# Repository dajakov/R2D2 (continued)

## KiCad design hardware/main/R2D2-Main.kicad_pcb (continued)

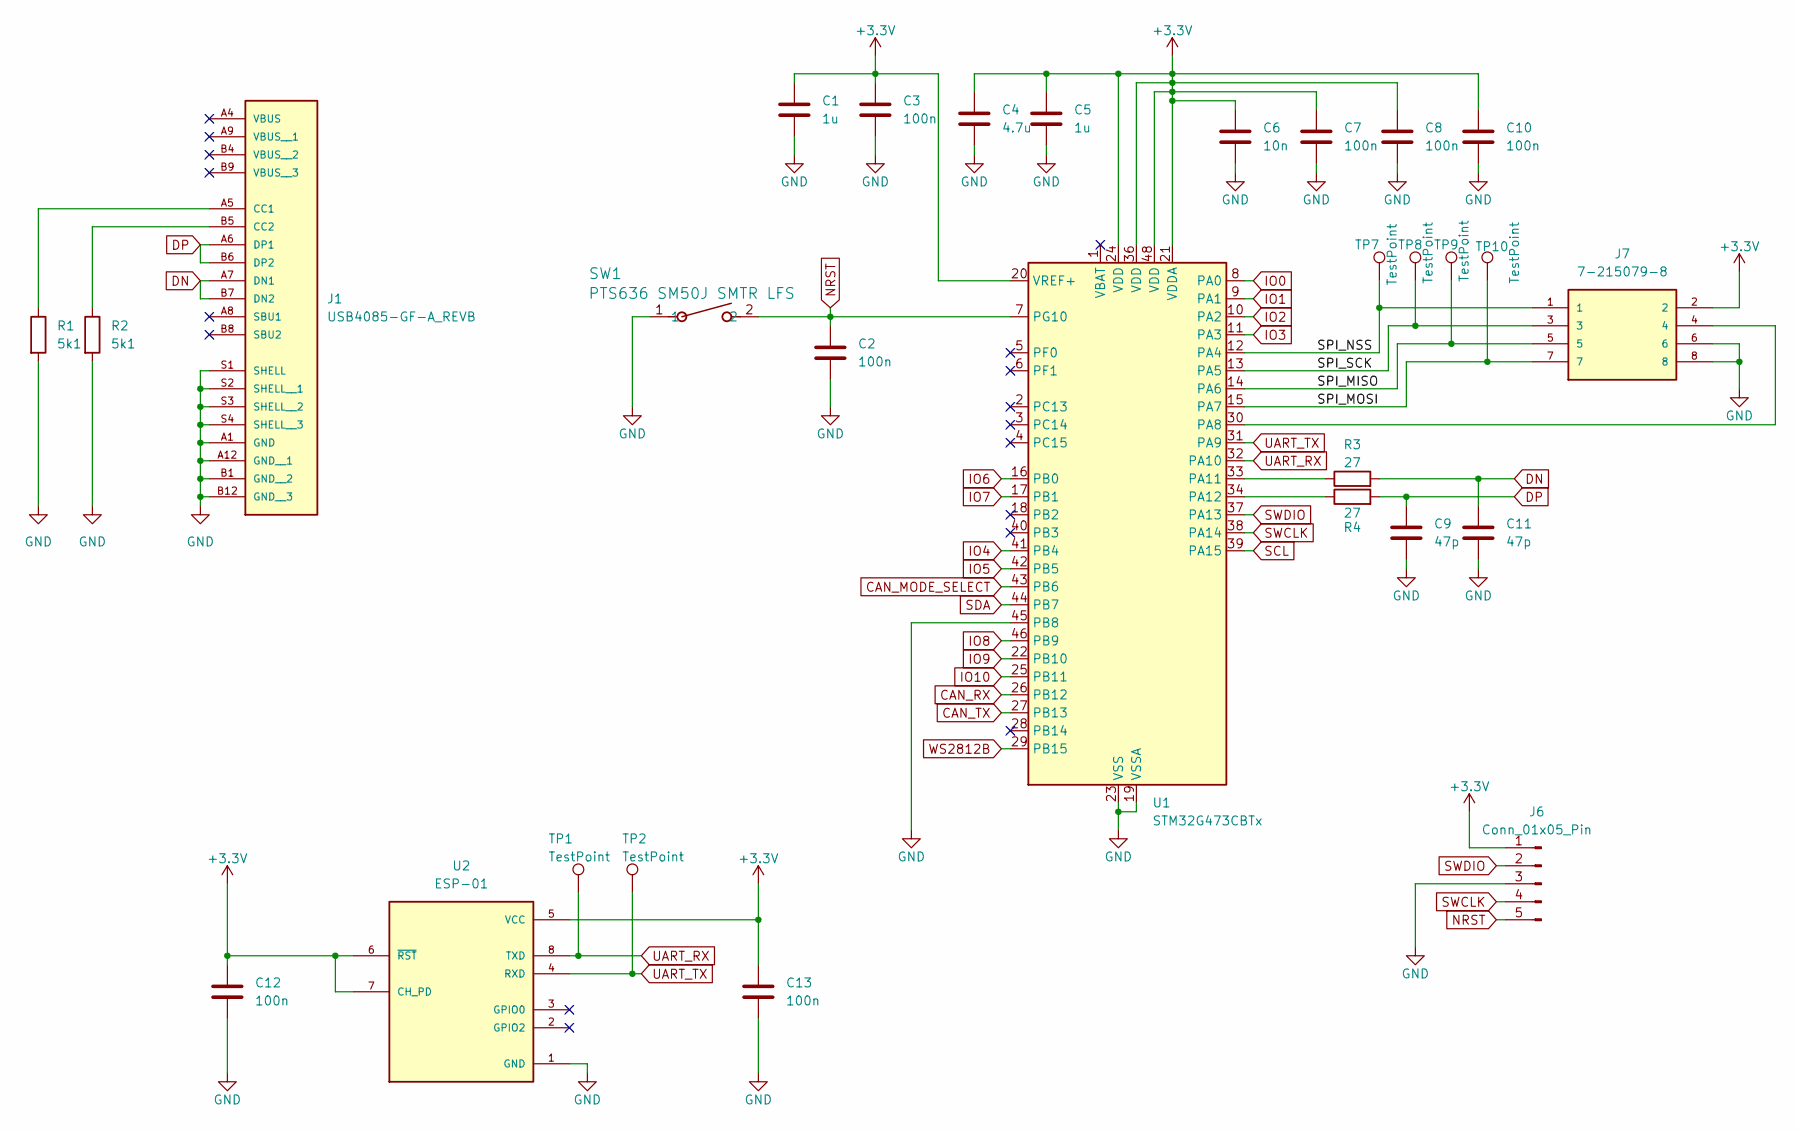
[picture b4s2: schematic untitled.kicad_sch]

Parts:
C1, C5: 1u; C_0603_1608Metric_Pad1.08x0.95mm_HandSolder
C2, C3, C7, C8, C10, C12, C13: 100n; C_0603_1608Metric_Pad1.08x0.95mm_HandSolder
C4: 4.7u; C_0603_1608Metric_Pad1.08x0.95mm_HandSolder
C6: 10n; C_0603_1608Metric_Pad1.08x0.95mm_HandSolder
C9, C11: 47p; C_0603_1608Metric_Pad1.08x0.95mm_HandSolder
J1: USB4085-GF-A_REVB; GCT_USB4085-GF-A_REVB; PARTREV B
J6: Conn_01x05_Pin; PinHeader_1x05_P2.54mm_Vertical
J7: 7-215079-8; TE_7-215079-8; PARTREV Y1
R1, R2: 5k1; R_0603_1608Metric_Pad0.98x0.95mm_HandSolder
R3, R4: 27; R_0603_1608Metric_Pad0.98x0.95mm_HandSolder
SW1: PTS636 SM50J SMTR LFS; SW_PTS636_CNK
TP1, TP2, TP7, TP8, TP9, TP10: TestPoint; TestPoint_Pad_D1.0mm
U1: STM32G473CBTx; LQFP48-7x7mm
U2: ESP-01; MODULE_ESP-01; PARTREV 1.0

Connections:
+3.3V: C1.1, C3.1, C4.1, C5.1, C6.1, C7.1, C8.1, C10.1, C12.1, C13.1, J6.1, J7.2, U1.20 (VREF+), U1.21 (VDDA), U1.24 (VDD), U1.36 (VDD), U1.48 (VDD), U2.5 (VCC), U2.6 (~RST), U2.7 (CH_PD); also elsewhere on the board
/Untitled Sheet/SPI_MISO: J7.5, TP9.1, U1.14 (PA6)
/Untitled Sheet/SPI_MOSI: J7.7, TP10.1, U1.15 (PA7)
/Untitled Sheet/SPI_NSS: J7.1, TP7.1, U1.12 (PA4)
/Untitled Sheet/SPI_SCK: J7.3, TP8.1, U1.13 (PA5)
CAN_MODE_SELECT: U1.43 (PB6); also elsewhere on the board
CAN_RX: U1.26 (PB12); also elsewhere on the board
CAN_TX: U1.27 (PB13); also elsewhere on the board
DN: C11.1, J1.A7 (DN1), J1.B7 (DN2), R3.2
DP: C9.1, J1.A6 (DP1), J1.B6 (DP2), R4.2
GND: C1.2, C2.2, C3.2, C4.2, C5.2, C6.2, C7.2, C8.2, C9.2, C10.2, C11.2, C12.2, C13.2, J1.A1 (GND), J1.A12 (GND__1), J1.B1 (GND__2), J1.B12 (GND__3), J1.S1 (SHELL), J1.S2 (SHELL__1), J1.S3 (SHELL__2), J1.S4 (SHELL__3), J6.3, J7.6, J7.8, R1.2, R2.2, SW1.1, U1.19 (VSSA), U1.23 (VSS), U1.35 (VSS), U1.45 (PB8), U1.47 (VSS), U2.1 (GND); also elsewhere on the board
IO0: U1.8 (PA0); also elsewhere on the board
IO1: U1.9 (PA1); also elsewhere on the board
IO2: U1.10 (PA2); also elsewhere on the board
IO3: U1.11 (PA3); also elsewhere on the board
IO4: U1.41 (PB4); also elsewhere on the board
IO5: U1.42 (PB5); also elsewhere on the board
IO6: U1.16 (PB0); also elsewhere on the board
IO7: U1.17 (PB1); also elsewhere on the board
IO8: U1.46 (PB9); also elsewhere on the board
IO9: U1.22 (PB10); also elsewhere on the board
IO10: U1.25 (PB11); also elsewhere on the board
NRST: C2.1, J6.5, SW1.2, U1.7 (PG10)
unnamed: J1.A5 (CC1), R1.1
unnamed: J1.B5 (CC2), R2.1
unnamed: J7.4, U1.30 (PA8)
unnamed: R3.1, U1.33 (PA11)
unnamed: R4.1, U1.34 (PA12)
SCL: U1.39 (PA15); also elsewhere on the board
SDA: U1.44 (PB7); also elsewhere on the board
SWCLK: J6.4, U1.38 (PA14)
SWDIO: J6.2, U1.37 (PA13)
UART_RX: TP1.1, U1.32 (PA10), U2.8 (TXD)
UART_TX: TP2.1, U1.31 (PA9), U2.4 (RXD)
WS2812B: U1.29 (PB15); also elsewhere on the board

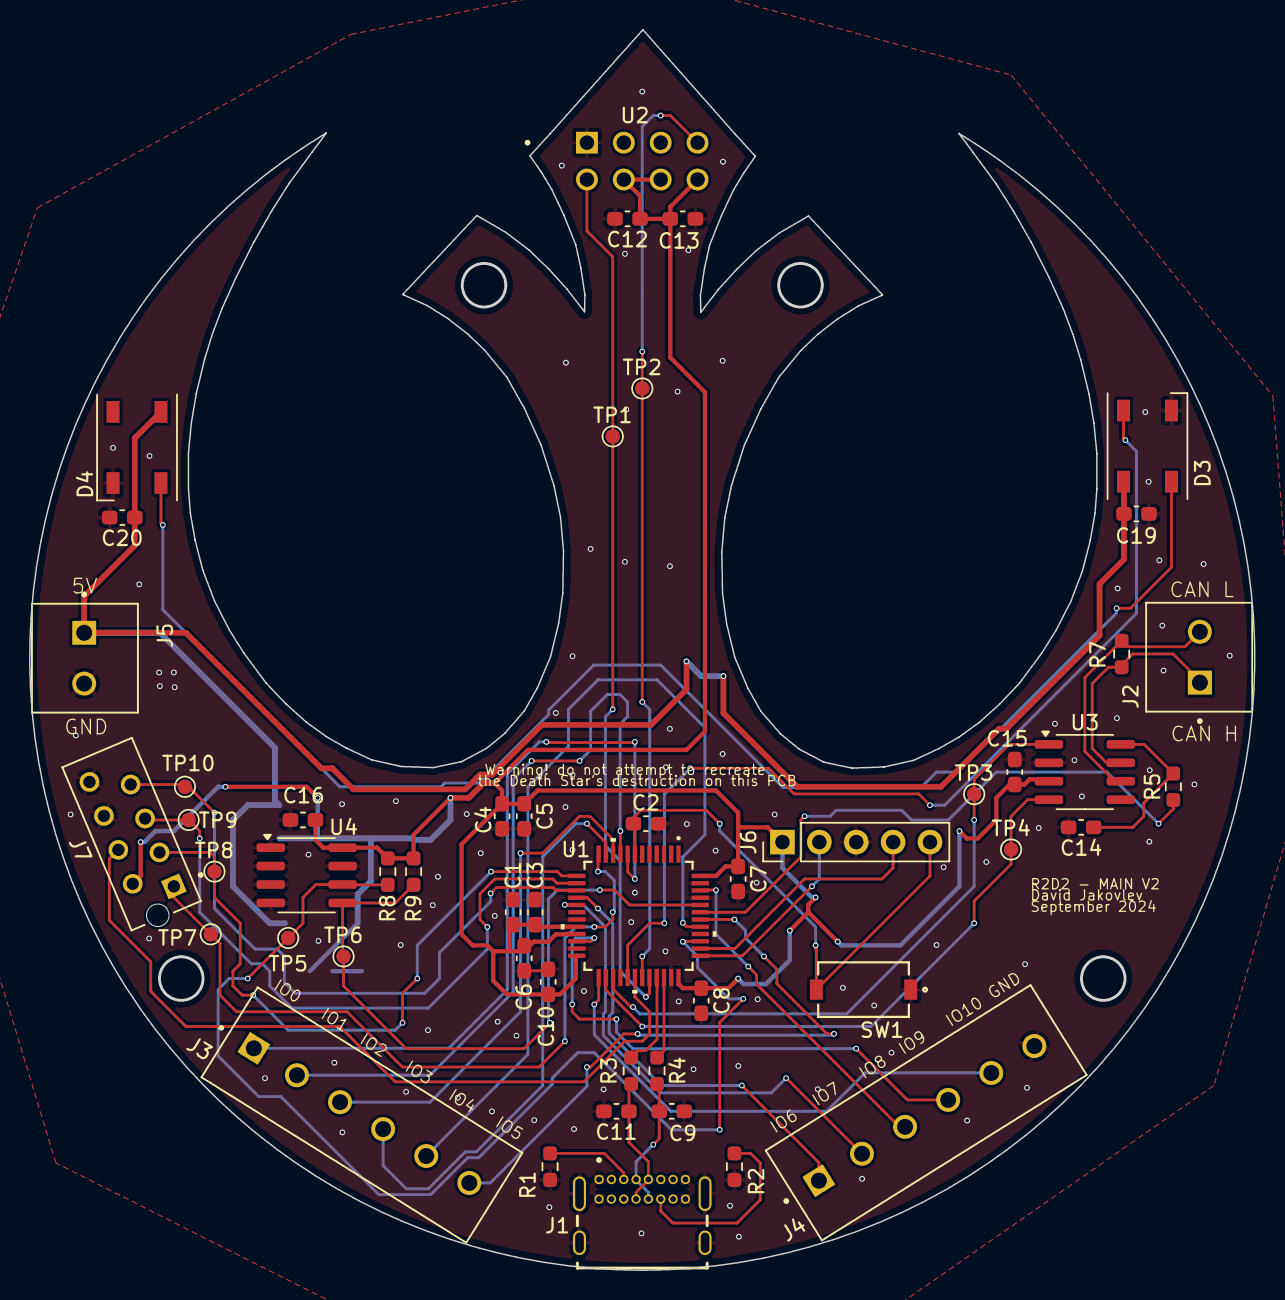
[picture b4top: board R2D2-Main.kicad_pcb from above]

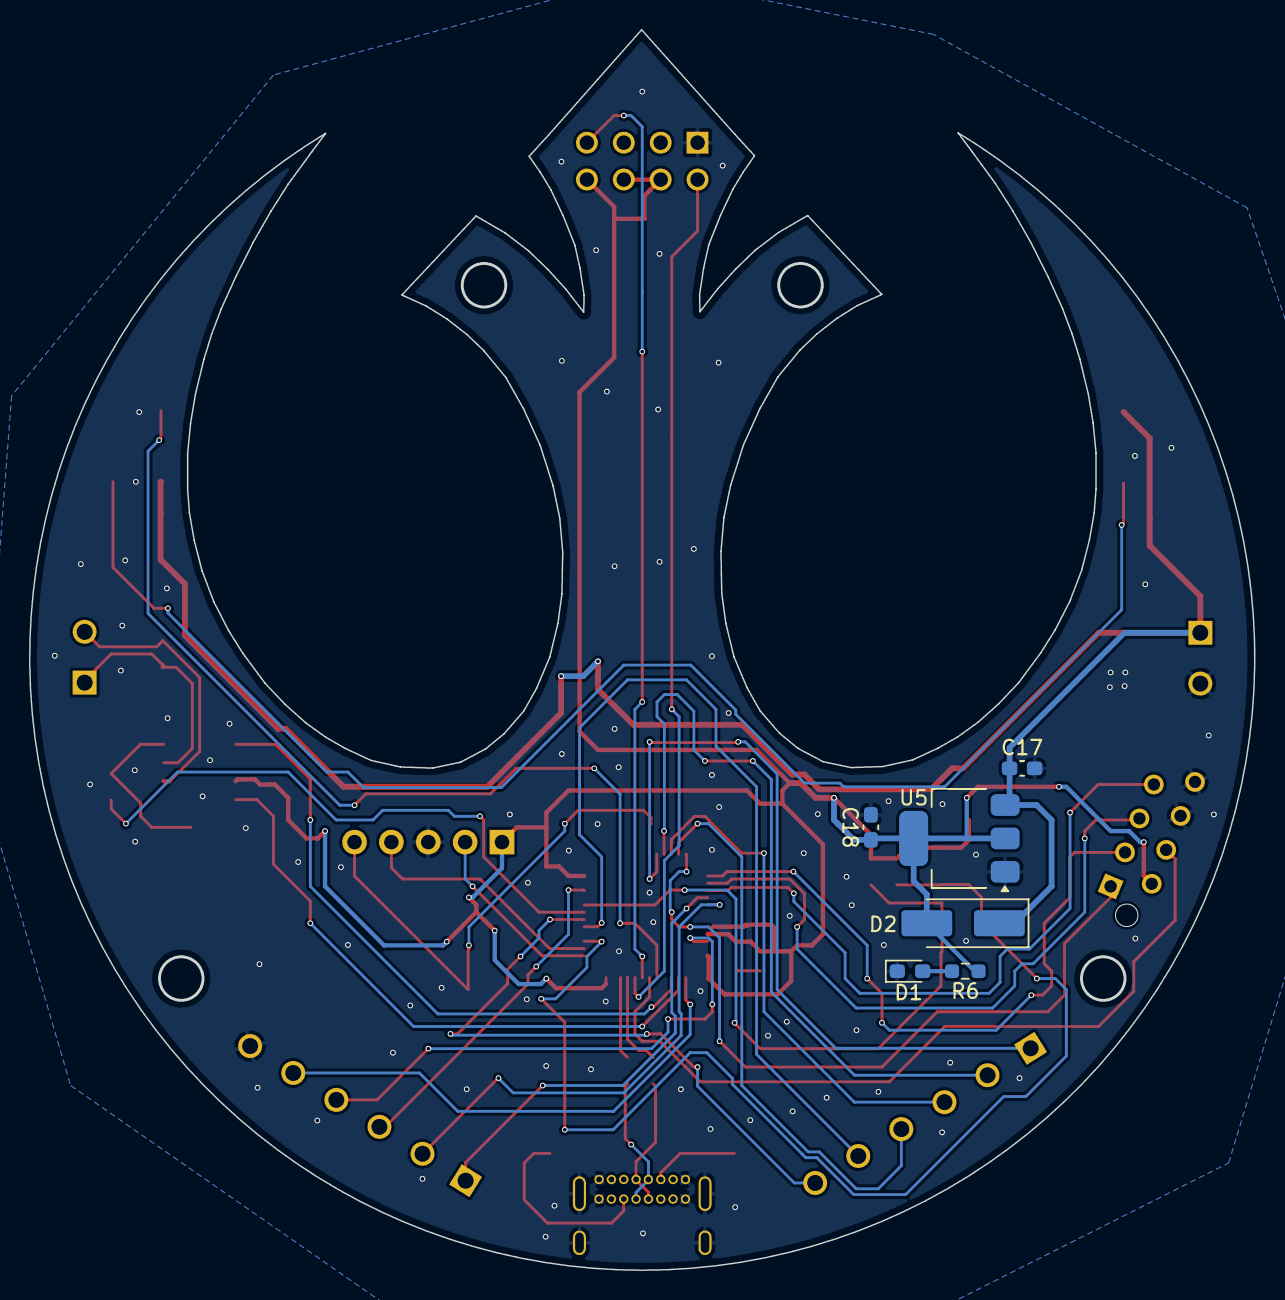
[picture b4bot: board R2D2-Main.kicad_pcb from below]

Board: 2 copper layers, 84.3 x 85.3 mm, 56 parts (6 on the bottom side), 41 nets.

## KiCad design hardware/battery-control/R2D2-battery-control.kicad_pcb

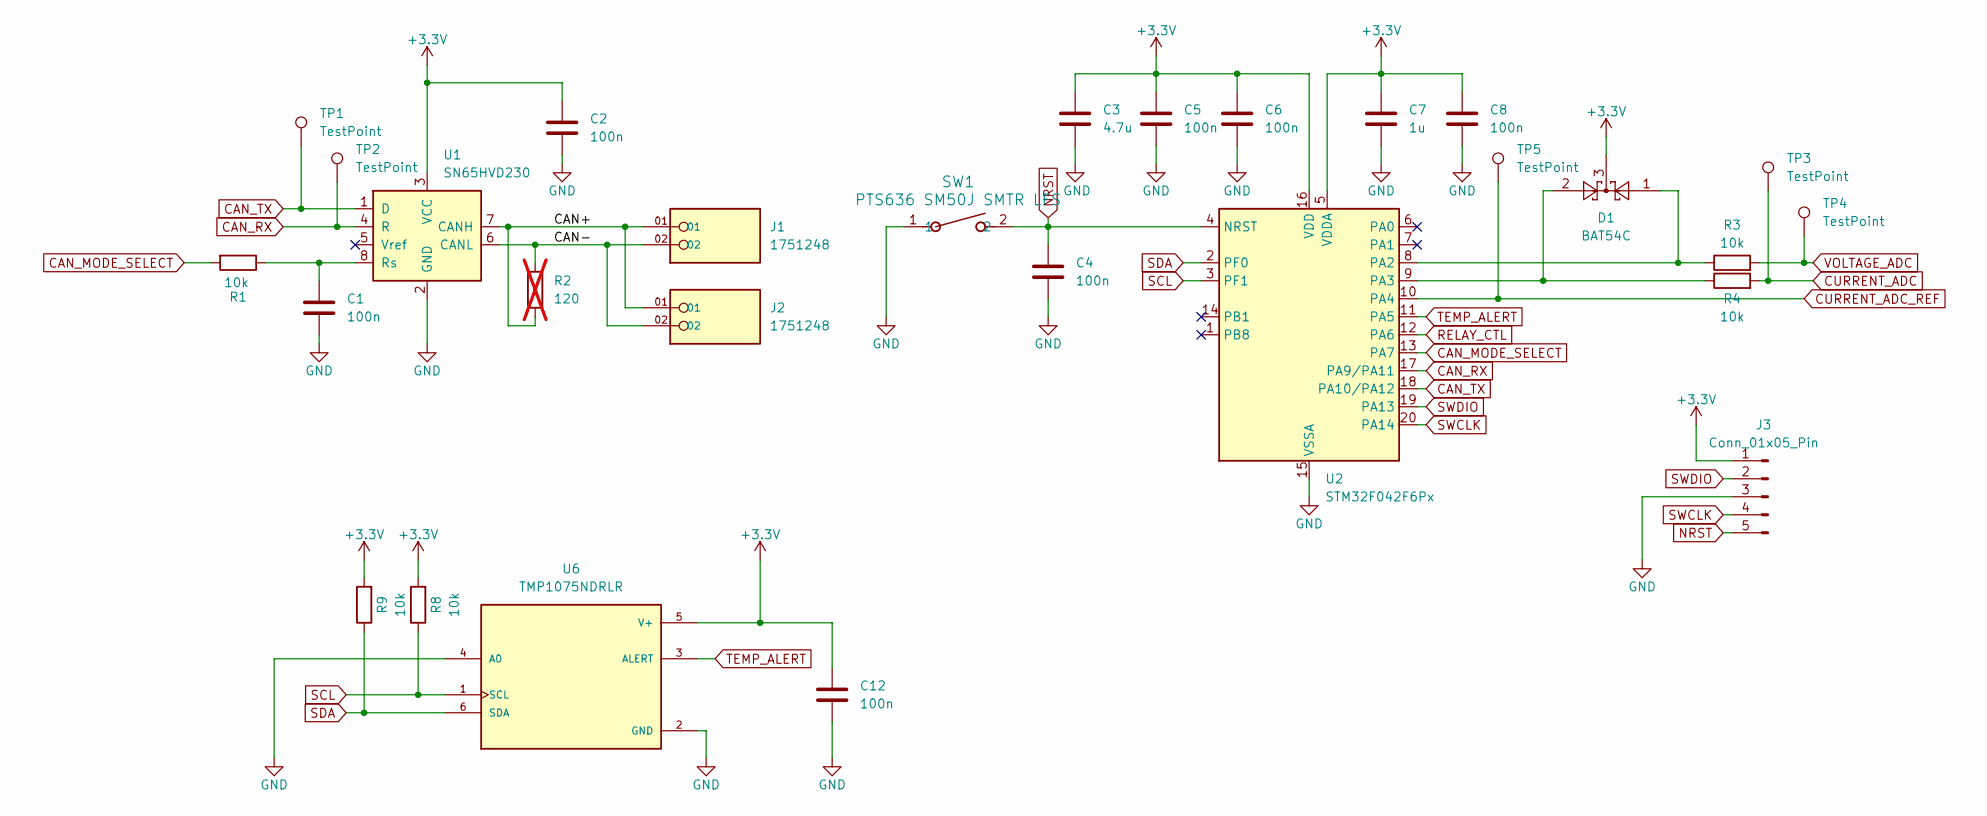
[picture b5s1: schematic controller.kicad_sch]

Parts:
C1, C2, C4, C5, C6, C8, C12: 100n; C_0603_1608Metric_Pad1.08x0.95mm_HandSolder
C3: 4.7u; C_0603_1608Metric_Pad1.08x0.95mm_HandSolder
C7: 1u; C_0603_1608Metric_Pad1.08x0.95mm_HandSolder
D1: BAT54C; SOT-23
J1, J2: 1751248; PHOENIX_1751248; PARTREV 03.03.2021
J3: Conn_01x05_Pin; PinHeader_1x05_P2.54mm_Horizontal
R1, R3, R4, R8, R9: 10k; R_0603_1608Metric_Pad0.98x0.95mm_HandSolder
R2: 120; R_0603_1608Metric_Pad0.98x0.95mm_HandSolder; not fitted
SW1: PTS636 SM50J SMTR LFS; SW_PTS636_CNK
TP1, TP2, TP3, TP4, TP5: TestPoint; TestPoint_Pad_D1.0mm
U1: SN65HVD230; SOIC-8_3.9x4.9mm_P1.27mm
U2: STM32F042F6Px; TSSOP-20_4.4x6.5mm_P0.65mm
U6: TMP1075NDRLR; SOT50P160X60-6N; PARTREV E

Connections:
+3.3V: C2.1, C3.1, C5.1, C6.1, C7.1, C8.1, C12.1, D1.3, J3.1, R8.2, R9.2, U1.3 (VCC), U2.5 (VDDA), U2.16 (VDD), U6.5 (V+); also elsewhere on the board
/controller/CAN+: J1.01, J2.01, R2.2, U1.7 (CANH)
/controller/CAN-: J1.02, J2.02, R2.1, U1.6 (CANL)
CAN_MODE_SELECT: R1.2, U2.13 (PA7)
CAN_RX: TP2.1, U1.4 (R), U2.17 (PA9/PA11)
CAN_TX: TP1.1, U1.1 (D), U2.18 (PA10/PA12)
CURRENT_ADC: R4.2, TP3.1; also elsewhere on the board
CURRENT_ADC_REF: TP5.1, U2.10 (PA4); also elsewhere on the board
GND: C1.2, C2.2, C3.2, C4.2, C5.2, C6.2, C7.2, C8.2, C12.2, J3.3, SW1.1, U1.2 (GND), U2.15 (VSSA), U6.2 (GND), U6.4 (A0); also elsewhere on the board
NRST: C4.1, J3.5, SW1.2, U2.4 (NRST)
unnamed: C1.1, R1.1, U1.8 (Rs)
unnamed: D1.1, R3.1, U2.8 (PA2)
unnamed: D1.2, R4.1, U2.9 (PA3)
RELAY_CTL: U2.12 (PA6); also elsewhere on the board
SCL: R8.1, U2.3 (PF1), U6.1 (SCL)
SDA: R9.1, U2.2 (PF0), U6.6 (SDA)
SWCLK: J3.4, U2.20 (PA14)
SWDIO: J3.2, U2.19 (PA13)
TEMP_ALERT: U2.11 (PA5), U6.3 (ALERT)
VOLTAGE_ADC: R3.2, TP4.1; also elsewhere on the board

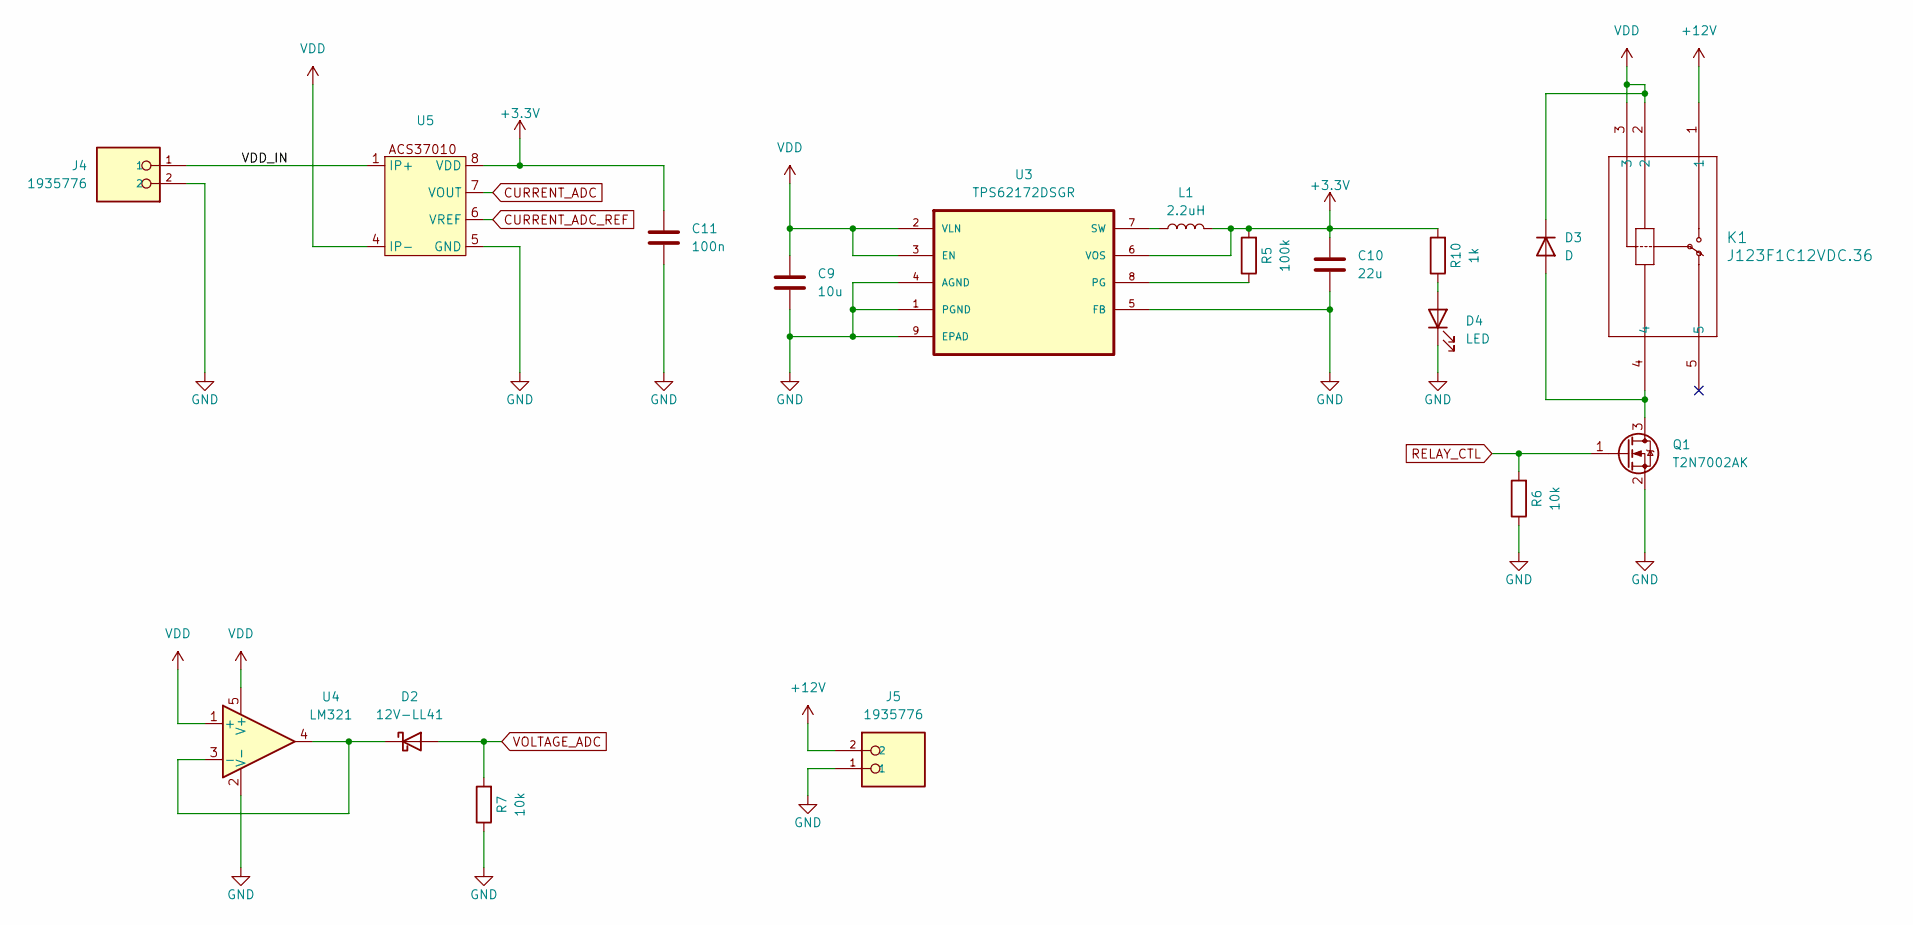
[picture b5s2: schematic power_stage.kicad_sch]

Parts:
C9: 10u; C_0603_1608Metric_Pad1.08x0.95mm_HandSolder
C10: 22u; C_0603_1608Metric_Pad1.08x0.95mm_HandSolder
C11: 100n; C_0603_1608Metric_Pad1.08x0.95mm_HandSolder
D2: 12V-LL41; D_MiniMELF
D3: D; D_SMA
D4: LED; LED_0603_1608Metric
J4, J5: 1935776; PHOENIX_1935776; PARTREV 19.10.2016
K1: J123F1C12VDC.36; RELAY5_J123F1C5VDC.36_CRS
L1: 2.2uH; L_0805_2012Metric
Q1: T2N7002AK; SOT-23
R5: 100k; R_0603_1608Metric_Pad0.98x0.95mm_HandSolder
R6, R7: 10k; R_0603_1608Metric_Pad0.98x0.95mm_HandSolder
R10: 1k; R_0603_1608Metric_Pad0.98x0.95mm_HandSolder
U3: TPS62172DSGR; SON50P200X200X80-9N
U4: LM321; SOT-23-5
U5: ACS37010

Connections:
+3.3V: C10.1, C11.1, L1.2, R5.2, R10.2, U3.6 (VOS), U5.8 (VDD); also elsewhere on the board
+12V: J5.2, K1.1
/Power Stage/VDD_IN: J4.1, U5.1 (IP+)
CURRENT_ADC: U5.7 (VOUT); also elsewhere on the board
CURRENT_ADC_REF: U5.6 (VREF); also elsewhere on the board
GND: C9.2, C10.2, C11.2, D4.1 (K), J4.2, J5.1, Q1.2 (S), R6.1, R7.1, U3.1 (PGND), U3.4 (AGND), U3.5 (FB), U3.9 (EPAD), U4.2 (V-), U5.5 (GND); also elsewhere on the board
unnamed: D2.1 (K), U4.3 (-), U4.4
unnamed: D3.2 (A), K1.4, Q1.3 (D)
unnamed: D4.2 (A), R10.1
unnamed: R5.1, U3.8 (PG)
unnamed: L1.1, U3.7 (SW)
RELAY_CTL: Q1.1 (G), R6.2; also elsewhere on the board
VDD: C9.1, D3.1 (K), K1.2, K1.3, U3.2 (VLN), U3.3 (EN), U4.1 (+), U4.5 (V+), U5.4 (IP-)
VOLTAGE_ADC: D2.2 (A), R7.2; also elsewhere on the board

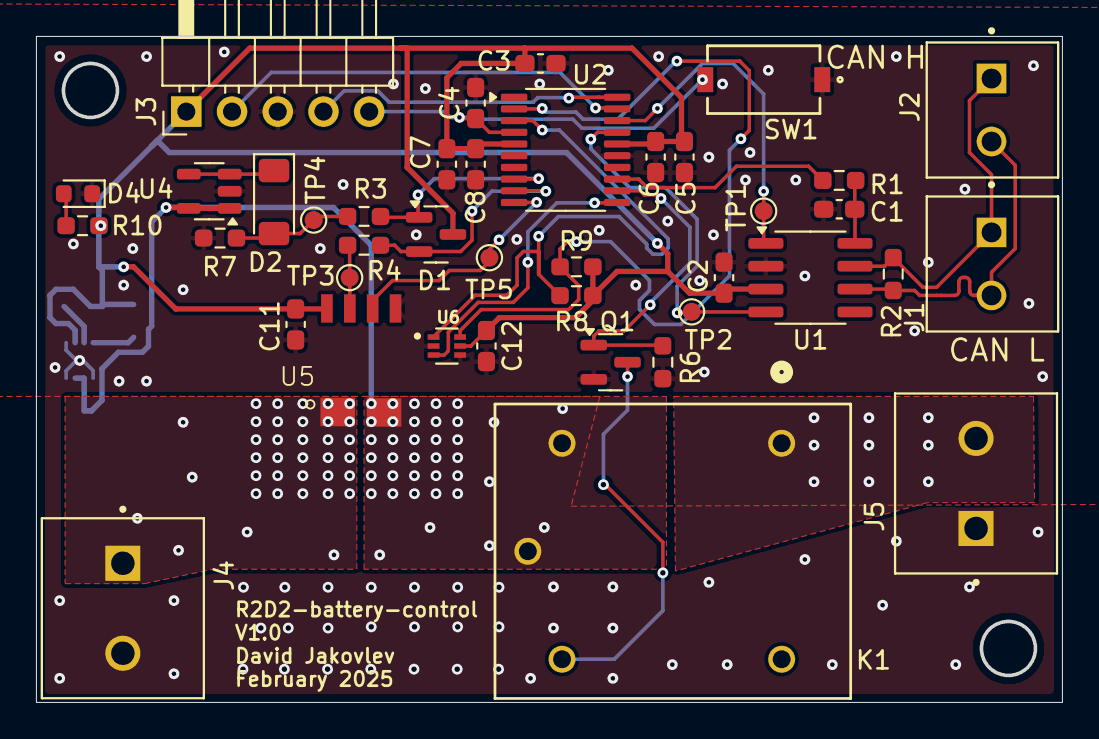
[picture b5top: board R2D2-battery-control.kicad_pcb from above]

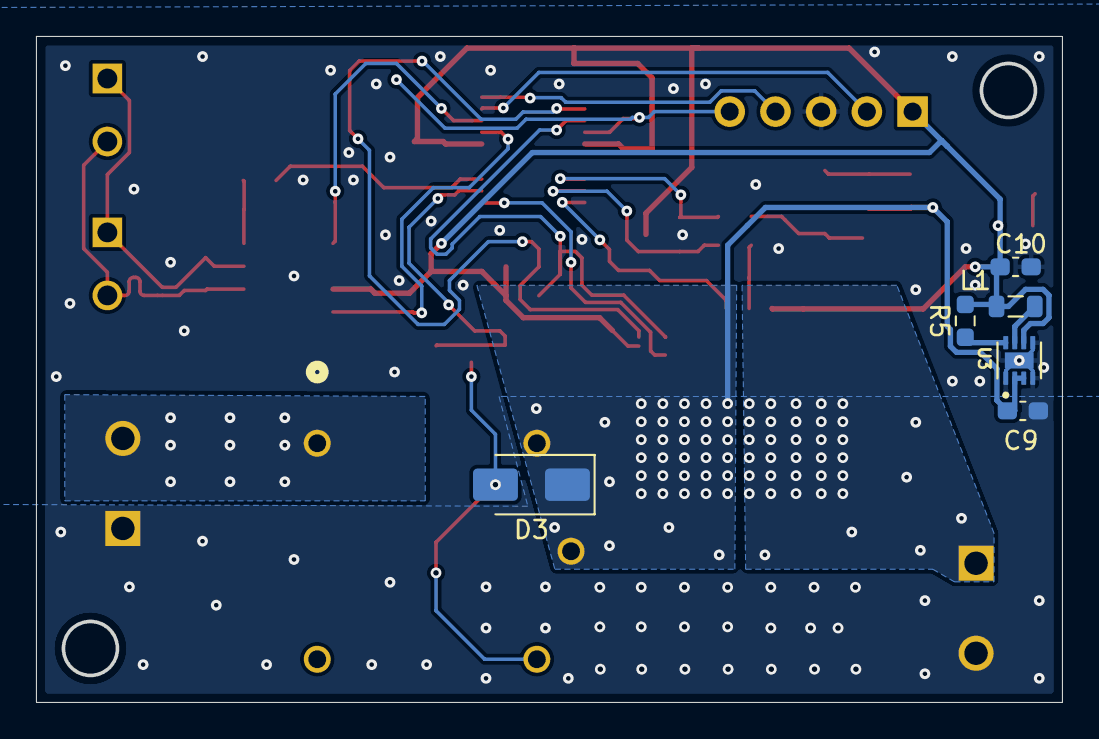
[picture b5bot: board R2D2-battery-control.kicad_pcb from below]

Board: 2 copper layers, 56.9 x 36.9 mm, 46 parts (6 on the bottom side), 28 nets.

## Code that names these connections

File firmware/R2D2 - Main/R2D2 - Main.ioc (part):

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Mcu.Name=STM32G473C(B-C-E)Tx
Mcu.Package=LQFP48
Mcu.UserName=STM32G473CBTx
PA0.GPIOParameters=GPIO_Label
PA0.GPIO_Label=TOUCH_CS
PA0.Signal=GPIO_Output
PA1.GPIOParameters=GPIO_Label
PA1.GPIO_Label=TOUCH_IRQ
PA1.Signal=GPIO_Output
PA10.Mode=Asynchronous
PA10.Signal=USART1_RX
PA11.Mode=Device
PA11.Signal=USB_DM
PA12.Mode=Device
PA12.Signal=USB_DP
PA13.Mode=Serial_Wire
PA13.Signal=SYS_JTMS-SWDIO
PA14.Mode=Serial_Wire
PA14.Signal=SYS_JTCK-SWCLK
PA15.Mode=I2C
PA15.Signal=I2C1_SCL
PA3.GPIOParameters=GPIO_Label
PA3.GPIO_Label=RST
PA3.Signal=GPIO_Output
PA4.GPIOParameters=GPIO_Label
PA4.GPIO_Label=SPI_NSS
PA4.Signal=GPIO_Output
PA5.Mode=Full_Duplex_Master
PA5.Signal=SPI1_SCK
PA6.Mode=Full_Duplex_Master
PA6.Signal=SPI1_MISO
PA7.Mode=Full_Duplex_Master
PA7.Signal=SPI1_MOSI
PA8.GPIOParameters=GPIO_Label
PA8.GPIO_Label=DC
PA8.Signal=GPIO_Output
PA9.Mode=Asynchronous
PA9.Signal=USART1_TX
PB12.GPIOParameters=GPIO_PuPd
PB12.GPIO_PuPd=GPIO_PULLUP
PB12.Mode=FDCAN_Activate
PB12.Signal=FDCAN2_RX
PB13.Mode=FDCAN_Activate
PB13.Signal=FDCAN2_TX
PB15.Signal=S_TIM15_CH2
PB6.GPIOParameters=GPIO_Label
PB6.GPIO_Label=CAN_MODE_SELECT
PB6.Signal=GPIO_Output
PB7.Mode=I2C
PB7.Signal=I2C1_SDA
RCC.HSE_VALUE=8000000
RCC.SYSCLKFreq_VALUE=170000000
RCC.SYSCLKSource=RCC_SYSCLKSOURCE_PLLCLK
board=custom

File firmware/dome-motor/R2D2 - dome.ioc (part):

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Mcu.Name=STM32F042F6Px
Mcu.Package=TSSOP20
Mcu.UserName=STM32F042F6Px
PA0.Mode=IN0
PA0.Signal=ADC_IN0
PA1.Mode=IN1
PA1.Signal=ADC_IN1
PA11.GPIOParameters=GPIO_PuPd
PA11.GPIO_PuPd=GPIO_PULLUP
PA11.Mode=CAN_Activate
PA11.Signal=CAN_RX
PA12.Mode=CAN_Activate
PA12.Signal=CAN_TX
PA13.Mode=Serial_Wire
PA13.Signal=SYS_SWDIO
PA14.Mode=Serial_Wire
PA14.Signal=SYS_SWCLK
PA2.GPIOParameters=GPIO_Label
PA2.GPIO_Label=HALL_SENSOR
PA2.Signal=GPXTI2
PA3.GPIOParameters=GPIO_Label
PA3.GPIO_Label=CAN_MODE_SELECT
PA3.Signal=GPIO_Output
PA4.GPIOParameters=PinState,GPIO_Label
PA4.GPIO_Label=MOTOR_CTL_IN1
PA4.PinState=GPIO_PIN_SET
PA4.Signal=GPIO_Output
PA5.Signal=S_TIM2_CH1_ETR
PA6.GPIOParameters=PinState,GPIO_Label
PA6.GPIO_Label=MOTOR_SLEEP
PA6.PinState=GPIO_PIN_SET
PA6.Signal=GPIO_Output
PA7.GPIOParameters=GPIO_Label
PA7.GPIO_Label=MOTOR_FAULT
PA7.Signal=GPXTI7
RCC.SYSCLKFreq_VALUE=40000000
RCC.SYSCLKSource=RCC_SYSCLKSOURCE_PLLCLK
board=custom

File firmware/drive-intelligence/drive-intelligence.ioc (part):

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Mcu.Name=STM32F042F6Px
Mcu.Package=TSSOP20
Mcu.UserName=STM32F042F6Px
PA11.Mode=CAN_Activate
PA11.Signal=CAN_RX
PA12.Mode=CAN_Activate
PA12.Signal=CAN_TX
PA13.Mode=Serial_Wire
PA13.Signal=SYS_SWDIO
PA14.Mode=Serial_Wire
PA14.Signal=SYS_SWCLK
PA5.GPIOParameters=GPIO_Label
PA5.GPIO_Label=IMU_INT1
PA5.Signal=GPXTI5
PA6.GPIOParameters=GPIO_Label
PA6.GPIO_Label=IMU_INT2
PA6.Signal=GPXTI6
PA7.GPIOParameters=GPIO_Label
PA7.GPIO_Label=CAN_MODE_SELECT
PA7.Signal=GPIO_Output
PB1.Signal=S_TIM3_CH4
PB8.GPIOParameters=GPIO_PuPd,GPIO_Label
PB8.GPIO_Label=CAN_address_select
PB8.GPIO_PuPd=GPIO_PULLUP
PB8.Signal=GPIO_Input
PF0-OSC_IN.GPIOParameters=GPIO_Pu
PF0-OSC_IN.GPIO_Pu=GPIO_PULLUP
PF0-OSC_IN.Mode=I2C
PF0-OSC_IN.Signal=I2C1_SDA
PF1-OSC_OUT.GPIOParameters=GPIO_Pu
PF1-OSC_OUT.GPIO_Pu=GPIO_PULLUP
PF1-OSC_OUT.Mode=I2C
PF1-OSC_OUT.Signal=I2C1_SCL
RCC.SYSCLKFreq_VALUE=40000000
RCC.SYSCLKSource=RCC_SYSCLKSOURCE_PLLCLK
board=custom

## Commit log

2025-02-13 initial source files
2025-02-15 added hw and fw info to readme
2025-02-15 main firmware: added battery indicator to display
2025-02-16 main firmware: improved battery indicator for display
2025-02-16 firmware: updated cproject settings and inital commit for .hex files
2025-02-17 cleaned files, added new image
2025-03-04 fw: drive-intelligence: IMU sensor and speed measurement working
2025-03-05 hw: drive: added a solder jumper for CAN address
2025-03-05 fw: drive: added left/right motor detection through gpio
2025-03-09 fw: changed byte meaning of CAN data
2025-03-09 hw: drive-intelligence: added solder jumper for left or right motor setting
2025-03-17 hw: battery-control: R6 should not be populated. The internal resistors of MCU are used instead
